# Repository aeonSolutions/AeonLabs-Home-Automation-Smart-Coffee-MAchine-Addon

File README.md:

[ ](https://discord.gg/hw3j3RwfJf)

[PCB-Prototyping-Catalogue](https://github.com/aeonSolutions/PCB-Prototyping-Catalogue)  >>  [Home-Automation](https://github.com/aeonSolutions/PCB-Prototyping-Catalogue/tree/main/Home-Automation)  >>  [Smart Home Appliances](https://github.com/aeonSolutions/PCB-Prototyping-Catalogue/tree/main/Home-Automation/Smart%20Home%20Appliances)  >>  [Kitchen](https://github.com/aeonSolutions/PCB-Prototyping-Catalogue/tree/main/Home-Automation/Smart%20Home%20Appliances/kitchen)  >>  Smart Coffee Machine

<p align="right">
 <a href="https://github-com.translate.goog/aeonSolutions/AeonLabs-Home-Automation-Smart-Coffee-MAchine-Addon?_x_tr_sl=en&_x_tr_tl=pt&_x_tr_hl=en&_x_tr_pto=wapp">Change Language</a> <br>
Last update: 15-11-2023
</p>

# Smart Coffee Machine add-on 
<sup>   **status: <a href="https://en.wikipedia.org/wiki/Minimum_viable_product">M.V.P.</a>** NOW SELLING on <a href="https://www.tindie.com/stores/aeonlabs/">Tindie.com</a>  </sup> <br>
 
## Intro
think about the possibility of ordering a cup of coffee directly from Telegram even before you arrive at the cafe on a sunny day.... or sitting inside on a rainy day.....

...imagine the coffee machine replying to you and asking if you want a lot or less sugar. do you want milk in your coffee? Better, what temperature do you want for your coffee.

<br>

### The Problem
Nowadays there are countless coffee machines however with limited to no smart functionality. With this new way of doing work remotely buying a cup of coffee for a colleague, friend or family is not possible.

### The idea
This Home Automation Smart Coffee Machine Addon is easy installation on any home or office coffee machine, to enable any vintage coffee machine connectivity to the internet (or a personal network). The PCB uses an ESP32 S3 packed with Bluetooth, BLE, and WiFi compatible with major software vendors such as Apple Home, Google Home, Matter/Zigbee, Home Assistant, and many others.
The custom firmware being coded includes the functionality of someone paying for a cup of coffee using any home banking App, Paypal, Stripe on any other means of payment. In return, it sends a receipt as proof a coffee was indeed brewed on the coffee machine.

If you prefer, can read this project on ....

- Autodesk's Intructables.com website, [here](https://www.instructables.com/member/mtpsilva/?publicPreview=true)
- Hackster.io website [here](https://www.hackster.io/mtpsilva/smart-add-on-for-the-philips-senseo-coffee-machine-06d9bf)
- Medium.com webiste [here](https://medium.com/@mtpsilva)

<br>

I've created a WhatsApp Chat for aditional support of feedback, join us [here](https://chat.whatsapp.com/FkNC7u83kuy2QRA5sqjBVg) !

<br>

**Functionalities available:** 

* Control water temperature;
* Low water detection in the water tank; 
* Order a cup of coffee (with the possibility control the quantity of coffee in the cup);
* Grind coffee beans.;
* Connect to a Nextion LCD Touch ;
* RGB LED;
* Magnetic Buzzer;

To all those looking for LCD touch solutions, this PCB features a connection to NEXTION LCD panels so one can order a cup of coffee using the LCD Touch. 

* This PCB can be powered using 220V AC or regular 5V DC. 

* Control of the coffee machine is made using a 220V relay or alternatively any other 3.3V switch. 

Great to do a restoration with this smart PCB add-on on any vintage coffee machine.

*Don't forget to LIKE, SHARE, and subscribe to the free whatsApp group* and if you liked this PCB consider buying me a cup of coffee. Links below.

<br>

###  Status
  The Smart Coffee Machine Add-on is now Fully functional.

I've contacted Signal ([www.signal.org](http://www.signal.org)) and Mesibo ([https://mesibo.com/](https://mesibo.com/)) App Developers and inquired them with the possibility of this open hardware smart coffee machine pcb add-on be integrated in their messager apps so anyone can order a cup of coffee during a messenger conversation / chat and also during a conference meeting. Stay tuned for updates. 

<br>

## Try it right now on Telegram 

Is now #official. Anyone can "buy me a coffee" on Telegram. Just start a conversation with **MiguelCoffeeMachineBot** [here](https://t.me/MiguelCoffeeMachineBot) and send a message `/start` to view available commands. 

Available commands:
 - `/start`                      : to view available commands on the Coffee Machine i have at my home
 - `/coffee`                     : to "buy" Miguel a cup of Coffee
 - `/tea`                        : to "buy" Miguel a cup of Tea
 - `/cappuccino`                 : to buy a cup of Cappuccino
 - `/decaf`                      : to buy a cup of decaf. coffee
 - `/accept`[long/normal/short]  : to accept an offer made by another person
 - `/status`                     : to view the current status of the Philips Senseo Coffee Machine

Try it out is free and is #FUN. No money is asked! Great for a meeting or a conversation online. No excuses not to have a cup of coffee with colleagues while working remotely. 

<br>

## OEM Firmware code
The OEM version of the firmware code can be found on the folder **firmware code**.  It has by default OTA updates, meaning the smart coffee machine add-on device automatically updates it self when newer updated versions made available here.  

**How to use the firmware code** <br>
Install all library dependecies (see below). <br>
unzip the "firmware code" folder and rename it with the name of the .ino file it contains. <br> 
Open the .ino file in Arduino Studio. <br>
Select the ESP32 S3 MCU / board from the menu, and then the code should compile. if not, follow the instructions shown in the debug console. <br>

**Library Dependencies** <br> 
This code uses my own ESP32 c++ class libraries to expedite development of code of ESP32 microcontrollers. 
- ✓ Aeonlabs Base Libraries [view](https://github.com/aeonSolutions/aeonlabs-ESP32-C-Base-Firmware-Libraries)
  
<br>

## Features requests 
  - Mobile App to control de coffee Machine over the network
  - Linux, Mac, Windows App to control de coffee Machine over the network

<br>

## Compatibility

<p align="center">

</p>

<br>

## Liked it ? Get a Free PCB for yourself
Send me your Device or hardware and i will design a custom PCB for it. Free of charge. Contact-me on WhatsApp or email for more info. 

<p align="center">

</p>

<br>

## Q&A WhatsApp Group
If you have any Questions or simply  like this kind of projects and want to stay updated with the latest research ideas and prototypes during the day and week, join the WhatsApp Group
[LDAD Lab & Prototyping](https://chat.whatsapp.com/FkNC7u83kuy2QRA5sqjBVg)

<br>

## Buy a fully assembled PCB
Alternatively, and if you do not want to build a PCB by yourself and like to buy one, you can do it here:

<p align="center">

 </p>

The price will be around 30eur plus postage fees.
(I will also deliver the assembled PCB with all the components in place at a fair aditonal cost).

<br>

#### Be supportive of my dedication and work towards technology education and buy me a coffee. Link below.

<br>
<br>

#### Philips Senseo Coffee Machine 
Don't forget to checkout some cool photos of assembly on a Philips Senseo Coffee Machine [here](https://github.com/aeonSolutions/AeonLabs-Home-Automation-Smart-Coffee-MAchine-Addon/tree/main/Philips%20Senseo)

## PCB Parts list (incomplete)
- DC2DC converter HX4002B x2 : https://s.click.aliexpress.com/e/_Ak7IPx
- Capacitor 100nF SMD 1206 : https://s.click.aliexpress.com/e/_AVdmzr
- Capacitor 2.2uF SMD 1206 : https://s.click.aliexpress.com/e/_AVdmzr
- Resistor SMD 1206 330R x3 : https://s.click.aliexpress.com/e/_A7OXrR
- ESP32 WROOM32 x1 : https://s.click.aliexpress.com/e/_AF7N6l
- LED RGB x1: https://s.click.aliexpress.com/e/_AccXHT
- RFID RC522 x1 (optional) : https://s.click.aliexpress.com/e/_Am0LAH

**to get the complete Part list in a BOM file, consider supporting this repostitory by making a small donation. Links on the side and at the top. Thank you** 

<br>

## Firmware Download 
one can use the PCB in the repository [AeonLabs-MCU-Burner-USB-to-UART-TTL](https://github.com/aeonSolutions/AeonLabs-MCU-Burner-USB-to-UART-TTL) to program the ESP32 WROOM32 MCU on this PCB.

<br>

## Other similar projects

- [Smart coffee machine on local network](https://github.com/cryptax/webpresso)

Prodigio smart coffee machines are only accessible through Bluetooth Low Energy (BLE). This project makes it possible to access them via HTTP/HTTPS, using a RPi 3 as BLE relay.

- [CoffeeMaker](https://github.com/ivanph1017/CoffeeMaker)

This is part of a project to manage a coffee maker at home from a Android mobile phone. It's made up of an Android app written in Kotlin as the front-end, Firebase service as the back-end and Raspberry PI 3 as a single board computer with a script written in Javascript running on Node.JS and integrated to a coffee maker with water level sensors.

The coffee maker can be turned on/off by the Android app. Nonetheless, it can only be kept turned on maximum of 1 hour. If such an amount of time has passed, it automatically turns off and it rests up by 5 minutes in order to be available of turning on again.

- [Coffee Machine Project](http://simcap.github.io/coffeemachine/)

In this Coffe Machine Project, your task is to implement the logic (starting from a simple class) that translates orders from customers of the coffee machine to the drink maker. Your code will use the drink maker protocol to send commands to the drink maker.

one can find more coffee machine open projectt, [here](https://github.com/topics/coffee-machine?l=java).

<br>

______________________________________________________________________________________________________________________________

### License
2022 Creative Commons Attribution-NonCommercial-ShareAlike 4.0 International

https://creativecommons.org/licenses/by-nc-sa/4.0/

### Own a copy of this work
if you like to own a copy of this work, you can buy it as a NFT or Ethereum. contact me for more details at mtpsilva@gmail.com

=====================================================================================
### Share this PCB board files

### Be supportive of my dedication and work towards technology education and buy me a coffee

<p align+"left">

<br>

</p>

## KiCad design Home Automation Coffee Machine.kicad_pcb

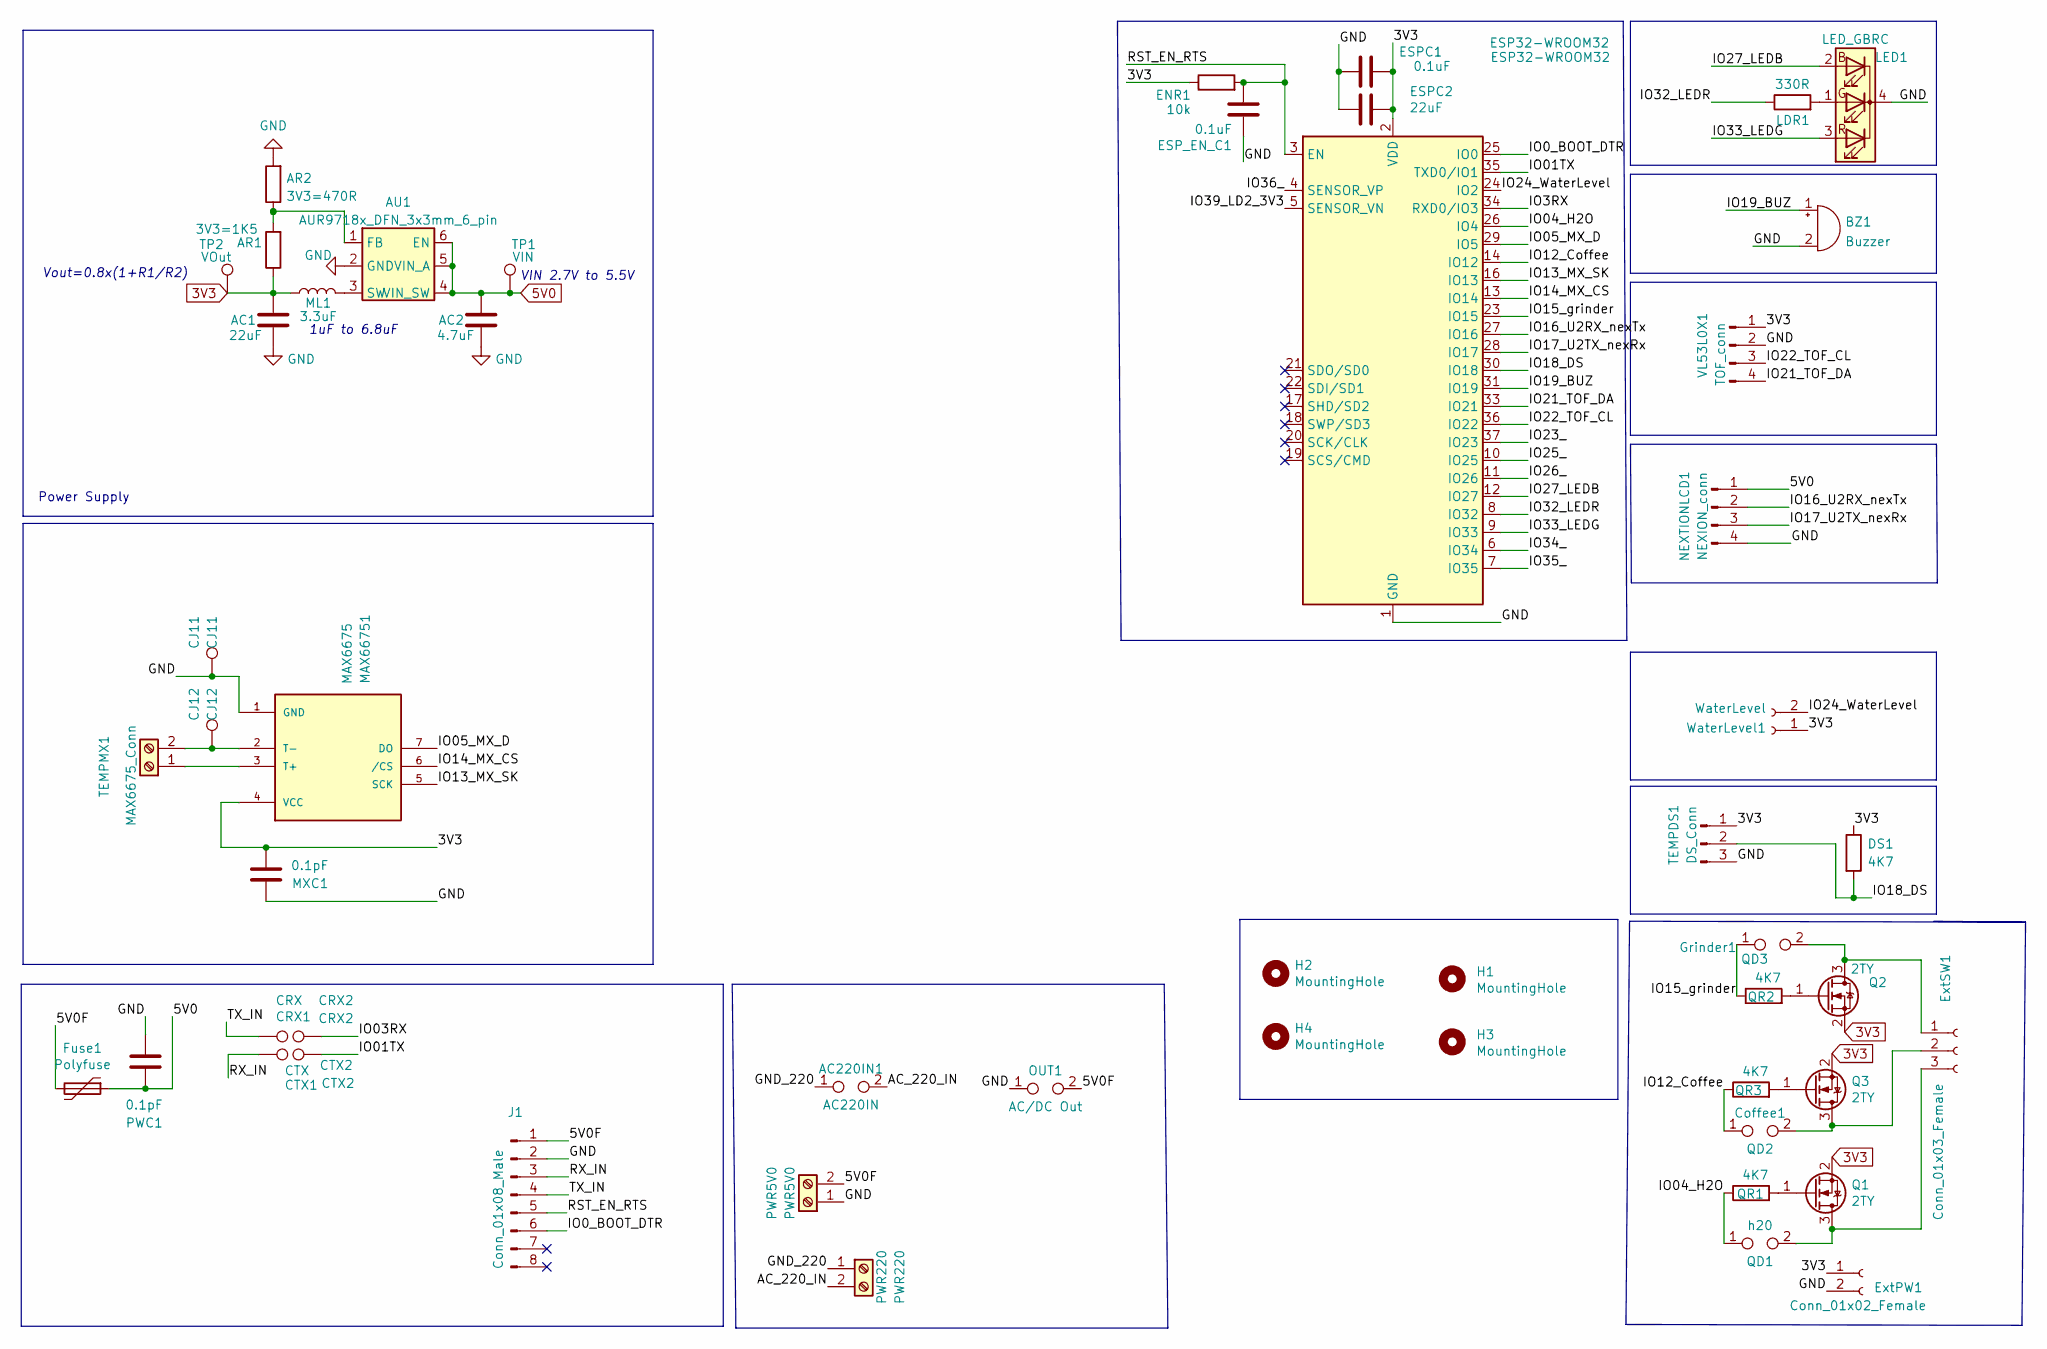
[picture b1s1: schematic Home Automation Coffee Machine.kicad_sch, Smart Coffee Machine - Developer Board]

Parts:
AC1: 22uF; C_0805_2012Metric_Pad1.18x1.45mm_HandSolder
AC2: 4.7uF; C_0805_2012Metric_Pad1.18x1.45mm_HandSolder
AC220IN1: AC220IN; TestPoint_2Pads_Pitch3.81mm_Drill1.3mm
AR1: 3V3=1K5; R_0805_2012Metric_Pad1.20x1.40mm_HandSolder
AR2: 3V3=470R; R_0805_2012Metric_Pad1.20x1.40mm_HandSolder
AU1: AUR9718x_DFN_3x3mm_6_pin; AUR9718 3x3mm 6 pin
BZ1: Buzzer; MagneticBuzzer_Kobitone_254-EMB84Q-RO
CJ11: CJ11; TestPoint_Pad_1.0x1.0mm
CJ12: CJ12; TestPoint_Pad_1.0x1.0mm
CRX1: CRX; TestPoint_Pad_1.0x1.0mm
CRX2: CRX2; TestPoint_Pad_1.0x1.0mm
CTX1: CTX; TestPoint_Pad_1.0x1.0mm
CTX2: CTX2; TestPoint_Pad_1.0x1.0mm
Coffee1: QD2; TestPoint_Pad_Bridge_1.0x1.0mm
DS1: 4K7; R_1206_3216Metric
ENR1: 10k; R_1206_3216Metric
ESP32-WROOM32: ESP32-WROOM32; ESP32-WROOM-32
ESPC1: 0.1uF; C_1206_3216Metric
ESPC2: 22uF; C_1206_3216Metric
ESP_EN_C1: 0.1uF; C_1206_3216Metric
ExtPW1: Conn_01x02_Female; JST_PH_B2B-PH-K_1x02_P2.00mm_Vertical
ExtSW1: Conn_01x03_Female; JST_PH_B3B-PH-K_1x03_P2.00mm_Vertical
Fuse1: Polyfuse; Fuse_1206_3216Metric
Grinder1: QD3; TestPoint_Pad_Bridge_1.0x1.0mm
H1, H2, H3, H4: MountingHole; MountingHole_3.2mm_M3_DIN965
J1: Conn_01x08_Male; SOIC_clipProgSmall
LDR1: 330R; R_1206_3216Metric
LED1: LED_GBRC; LED_RGB_5050-6
MAX66751: MAX6675; SOIC-8W_5.3x5.3mm_P1.27mm
ML1: 3.3uF; L_1210_3225Metric
MXC1: 0.1pF; C_1206_3216Metric
NEXTIONLCD1: NEXION_conn; JST_EH_B4B-EH-A_1x04_P2.50mm_Vertical
OUT1: AC/DC Out; TestPoint_2Pads_Pitch2.54mm_Drill0.8mm
PWC1: 0.1pF; C_True_1206_3216Metric
PWR5V0: PWR5V0; TerminalBlock_4Ucon_1x02_P3.50mm_Vertical
PWR220: PWR220; TerminalBlock_bornier-2_P5.08mm
Q1, Q2, Q3: 2TY; SOT-23
QR1, QR2, QR3: 4K7; R_0805_2012Metric_Pad1.20x1.40mm_HandSolder
TEMPDS1: DS_Conn; JST_EH_B3B-EH-A_1x03_P2.50mm_Vertical
TEMPMX1: MAX6675_Conn; TerminalBlock_4Ucon_1x02_P3.50mm_Vertical
TP1: VIN; TestPoint_Pad_D1.0mm
TP2: VOut; TestPoint_Pad_D1.0mm
VL53L0X1: TOF_conn; JST_EH_B4B-EH-A_1x04_P2.50mm_Vertical
WaterLevel1: WaterLevel; JST_EH_B2B-EH-A_1x02_P2.50mm_Vertical
h20: QD1; TestPoint_Pad_Bridge_1.0x1.0mm

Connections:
3V3: AC1.1, AR1.1, DS1.1, ENR1.1, ESP32-WROOM32.2 (VDD), ESPC1.1, ESPC2.1, ExtPW1.1, MAX66751.4 (VCC), ML1.1, MXC1.2, Q1.2 (S), Q2.2 (S), Q3.2 (S), TEMPDS1.1, TP2.1, VL53L0X1.1, WaterLevel1.1
/5V0F: Fuse1.2, J1.1, OUT1.2, PWR5V0.2
/AC_220_IN: AC220IN1.2, PWR220.2
/GND_220: AC220IN1.1, PWR220.1
/IO0_BOOT_DTR: ESP32-WROOM32.25 (IO0), J1.6
/IO01TX: CTX2.1, ESP32-WROOM32.35 (TXD0/IO1)
/IO3RX: ESP32-WROOM32.34 (RXD0/IO3)
/IO03RX: CRX2.1
/IO04_H2O: ESP32-WROOM32.26 (IO4), QR1.1, h20.1
/IO05_MX_D: ESP32-WROOM32.29 (IO5), MAX66751.7 (DO)
/IO12_Coffee: Coffee1.1, ESP32-WROOM32.14 (IO12), QR3.1
/IO13_MX_SK: ESP32-WROOM32.16 (IO13), MAX66751.5 (SCK)
/IO14_MX_CS: ESP32-WROOM32.13 (IO14), MAX66751.6 (/CS)
/IO15_grinder: ESP32-WROOM32.23 (IO15), Grinder1.1, QR2.1
/IO16_U2RX_nexTx: ESP32-WROOM32.27 (IO16), NEXTIONLCD1.2
/IO17_U2TX_nexRx: ESP32-WROOM32.28 (IO17), NEXTIONLCD1.3
/IO18_DS: DS1.2, ESP32-WROOM32.30 (IO18), TEMPDS1.2
/IO19_BUZ: BZ1.1 (-), ESP32-WROOM32.31 (IO19)
/IO21_TOF_DA: ESP32-WROOM32.33 (IO21), VL53L0X1.4
/IO22_TOF_CL: ESP32-WROOM32.36 (IO22), VL53L0X1.3
/IO23_: ESP32-WROOM32.37 (IO23)
/IO24_WaterLevel: ESP32-WROOM32.24 (IO2), WaterLevel1.2
/IO25_: ESP32-WROOM32.10 (IO25)
/IO26_: ESP32-WROOM32.11 (IO26)
/IO27_LEDB: ESP32-WROOM32.12 (IO27), LED1.2 (BA)
/IO32_LEDR: ESP32-WROOM32.8 (IO32), LDR1.1
/IO33_LEDG: ESP32-WROOM32.9 (IO33), LED1.3 (RA)
/IO34_: ESP32-WROOM32.6 (IO34)
/IO35_: ESP32-WROOM32.7 (IO35)
/IO36_: ESP32-WROOM32.4 (SENSOR_VP)
/IO39_LD2_3V3: ESP32-WROOM32.5 (SENSOR_VN)
/RST_EN_RTS: ENR1.2, ESP32-WROOM32.3 (EN), ESP_EN_C1.2, J1.5
/RX_IN: CTX1.1, J1.3
/TX_IN: CRX1.1, J1.4
unnamed: AR1.2, AR2.1, AU1.1 (FB)
unnamed: AU1.3 (SW), ML1.2
unnamed: CJ12.1, MAX66751.2 (T-), TEMPMX1.2
unnamed: Coffee1.2, ExtSW1.2, Q3.3 (D)
unnamed: ExtSW1.1, Grinder1.2, Q2.3 (D)
unnamed: ExtSW1.3, Q1.3 (D), h20.2
unnamed: LDR1.2, LED1.1 (GA)
unnamed: MAX66751.3 (T+), TEMPMX1.1
unnamed: Q1.1 (G), QR1.2
unnamed: Q2.1 (G), QR2.2
unnamed: Q3.1 (G), QR3.2

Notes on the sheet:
Vout=0.8x(1+R1/R2)
1uF to 6.8uF
Power Supply
VIN 2.7V to 5.5V

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
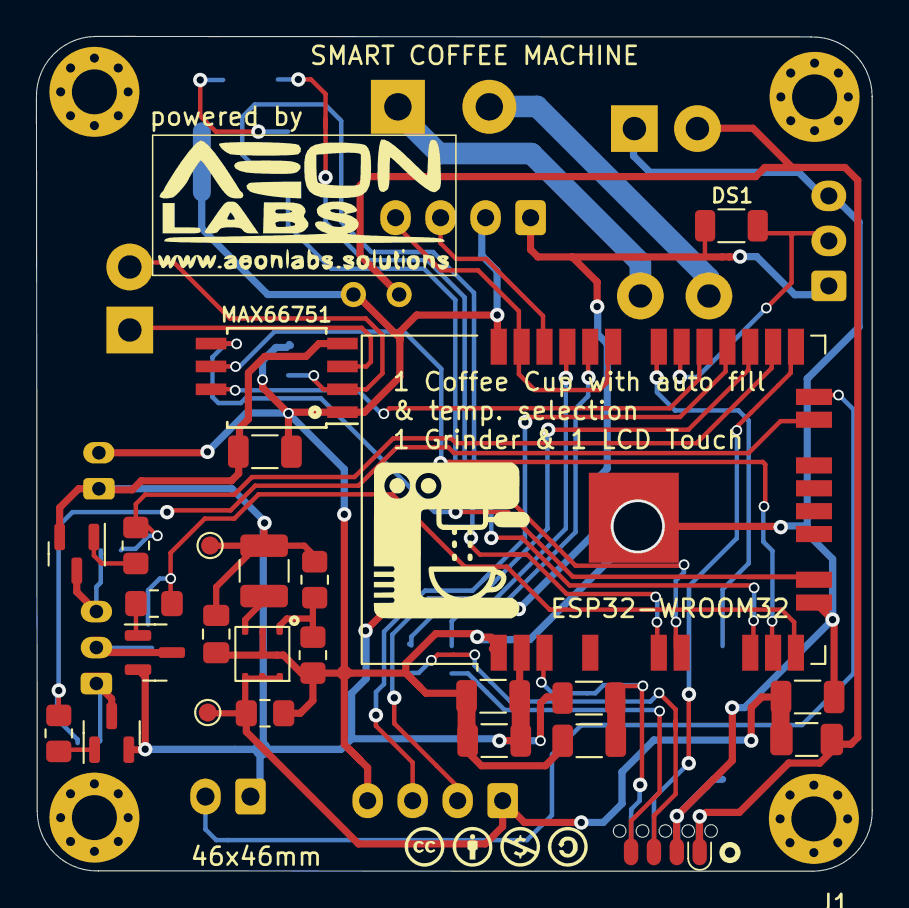
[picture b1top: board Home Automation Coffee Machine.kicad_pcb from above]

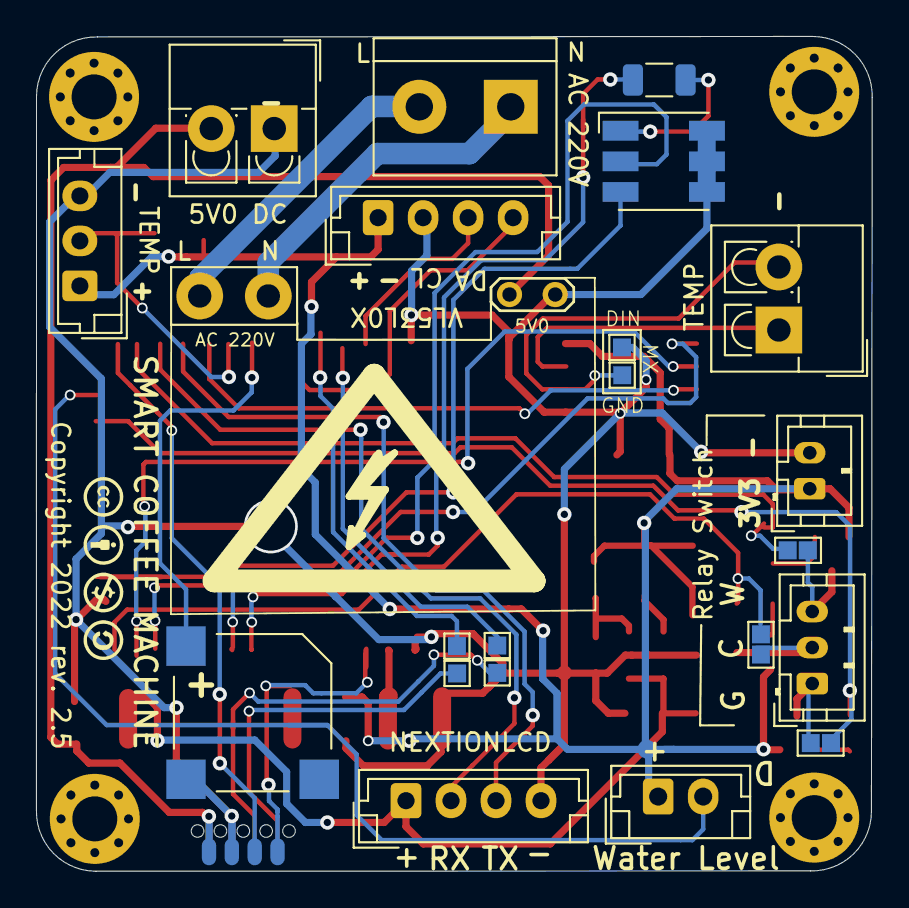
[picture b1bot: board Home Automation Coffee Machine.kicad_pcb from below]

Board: 2 copper layers, 46.4 x 46.4 mm, 52 parts (23 on the bottom side), 38 nets.

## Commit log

2022-04-01 init commit
2022-06-04 update Philips Senseo Coffee Machine
2022-06-04 update photos
2022-06-06 revision 2.3
2022-07-04 rev. 2.4
    improved relay connectivity. New 3.3V power converter.
2022-08-18 rev. 2.5
    correction to the power supply.

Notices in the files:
Home Automation Coffee Machine.kicad_pcb:
Copyright 2022 rev. 2.5
License Creative Commons 2022
